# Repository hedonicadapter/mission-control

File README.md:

# Mission Control
Custom ergonomic keeb with ergogen and a ZMK shield
- designed for a flex pcb
- n!n v2 + n!view
- ec11/ec12 encoder
- combination of mx and choc
- trackball (pmw3610)

*Take this with a grain of salt, I'm just experimenting and rarely know what I'm doing*

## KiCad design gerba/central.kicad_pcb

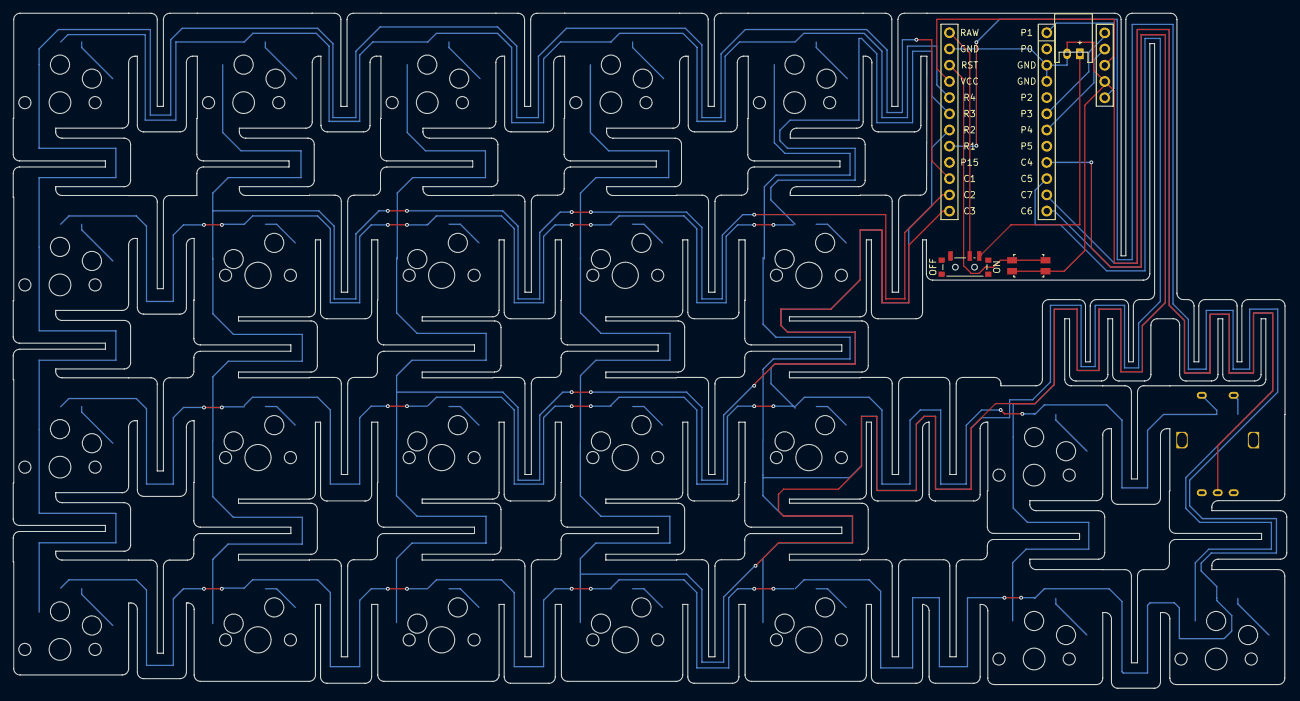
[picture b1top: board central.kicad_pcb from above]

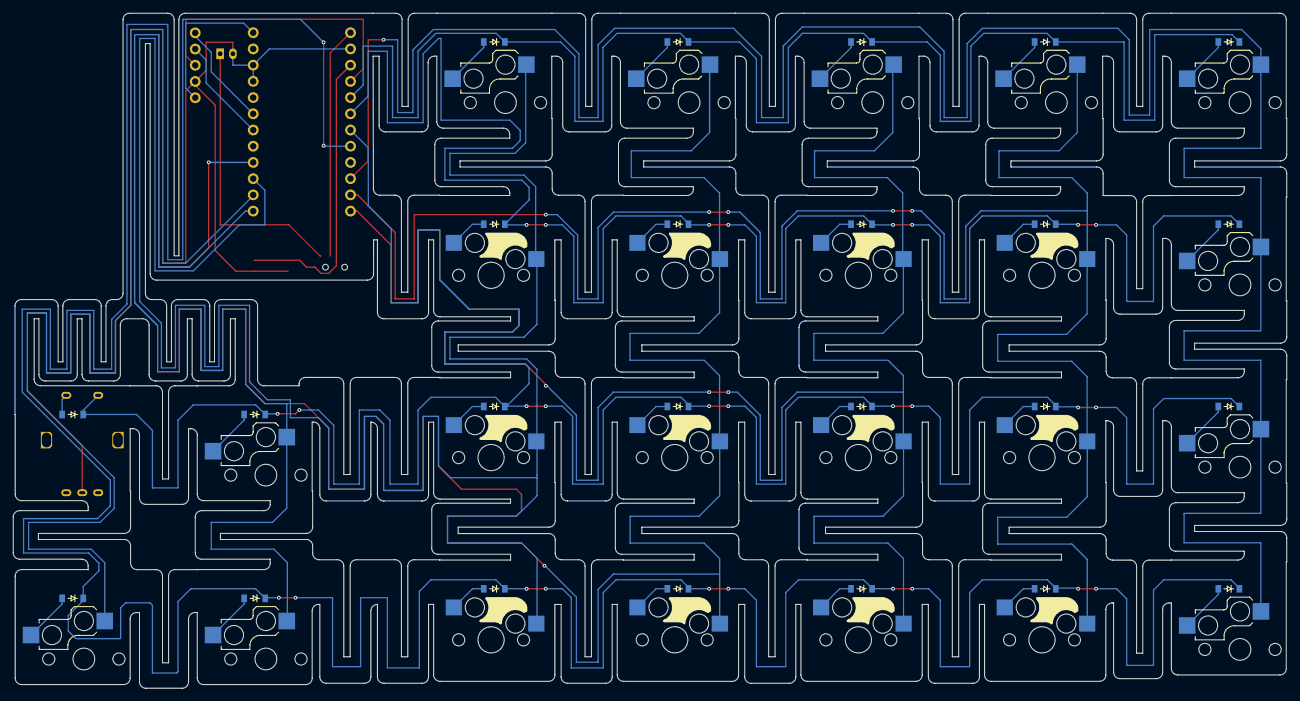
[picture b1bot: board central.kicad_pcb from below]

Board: 2 copper layers, 199.5 x 105.7 mm, 53 parts (47 on the bottom side), 43 nets.

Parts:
D1, D2, D3, D4, D5, D6, D7, D8, D9, D10, D11, D12, D13, D14, D15, D16, D17, D18, D19, D20, D21, D22, D23, D24: diode_tht_sod123
DISP1: display_nice_view
JST1: JST_PH_S2B-PH-K_02x2.00mm_Angled
MCU1: mcu_nice_nano
PWR1: power_switch_smd_side
RE1: rotary_encoder_ec11_ec12
RST1: reset_switch_smd_side
S1, S2, S3, S4, S5, S6, S7, S8, S9, S10, S11, S12: switch_mx
S13, S14, S15, S16, S17, S18, S19, S20, S21, S22, S23: switch_choc_v1_v2

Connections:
C1: MCU1.15, S13.1, S14.1, S15.1, S16.1
C2: MCU1.14, S1.1, S2.1, S3.1, S17.1
C3: MCU1.13, S4.1, S5.1, S6.1, S18.1
C4: MCU1.9, S7.1, S8.1, S9.1, S19.1
C5: MCU1.10, S10.1, S11.1, S12.1, S20.1
C6: MCU1.12, S21.1, S22.1
C7: MCU1.11, S23.1
GND: DISP1.2, JST1.2, MCU1.3, MCU1.4, MCU1.23, RE1.B, RST1.1, RST1.3
P1: DISP1.1, MCU1.1
P3: DISP1.5, MCU1.6
P4: DISP1.4, MCU1.7
R1: D1.1, D5.1, D9.1, D13.1, D17.1, D21.1, D23.1, MCU1.17
R2: D2.1, D6.1, D10.1, D14.1, D18.1, D22.1, D24.1, MCU1.18, RE1.S1
R3: D3.1, D7.1, D11.1, D15.1, D19.1, MCU1.19
R4: D4.1, D8.1, D12.1, D16.1, D20.1, MCU1.20
RAW: MCU1.24, PWR1.2
RST: MCU1.22, RST1.2, RST1.4
VCC: DISP1.3, MCU1.21
index_bottom: D17.2, S10.2
index_home: D18.2, S11.2
index_num: D20.2, S20.2
index_top: D19.2, S12.2
layer_one: D21.2, S21.2
layer_two: D22.2, S22.2
middle_bottom: D13.2, S7.2
middle_home: D14.2, S8.2
middle_num: D16.2, S19.2
middle_top: D15.2, S9.2
outer_bottom: D1.2, S13.2
outer_home: D2.2, S14.2
outer_num: D4.2, S16.2
outer_top: D3.2, S15.2
pinky_bottom: D5.2, S1.2
pinky_home: D6.2, S2.2
pinky_num: D8.2, S17.2
pinky_top: D7.2, S3.2
pos: JST1.1, PWR1.3
ring_bottom: D9.2, S4.2
ring_home: D10.2, S5.2
ring_num: D12.2, S18.2
ring_top: D11.2, S6.2
space_one: D23.2, S23.2
space_two: D24.2, RE1.S2

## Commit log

2024-11-21 init
2024-11-21 params
2024-11-22 trackpoint
2024-11-22 displays
2024-11-22 encoda
2024-11-22 stuff
2024-11-22 nets
2024-11-23 mirrored diodes fix
2024-11-24 screw holes and hand measurement
2024-11-24 proper outline
2024-11-24 choc thumbs
2024-11-25 choc encoda
2024-12-01 trackball footprint
2025-01-01 done maybe
2025-01-04 trackball
2025-02-12 redoing i guess
2025-02-14 outline done
2025-02-14 footprints done basicly
2025-02-14 hand_le review help
2025-02-14 netting and rounding
2025-02-15 pmw3610 pinout footprint
2025-02-15 added zmk config into this
2025-02-15 removed keycaps
2025-02-15 readme
2025-03-22 minimal repro
2025-03-22 fixed row/col pins
2025-03-22 row2col -> col2row
2025-03-22 removed config_usb=y
2025-03-22 col2row -> row2col
2025-03-22 encoder pings and enable
2025-03-22 BLE experimental features
2025-03-22 BLE passkey entry
2025-03-22 BT ctlr phy 2m
2025-03-22 spam fix
2025-03-22 no ble stuff
